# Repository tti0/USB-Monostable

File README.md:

# USB-Monostable

- An in-line timer/monostable switch for 5 V USB power, with a PCB based around the [555 timer](https://www.ti.com/product/NE555) and [SiP32508 load switch](https://www.vishay.com/docs/62754/sip32508.pdf) ICs.

_Populated USB-Monostable PCB_

- Pressing the "On" button causes the switch between the input and output USB power lines to close, reopening after a customisable and fixed time period has elapsed.
- Pressing the "Reset" button causes the switch to immediately open.
- Optional indicator LED reflects the switch status.
- USB data lines are not passed through.
- Current draw when the switch is open is under than 1 mA at 5 V.
- Slim physical footprint (20 x 60 mm) allows the switch to be placed in-line, between a power supply and downstream device.
- Uses robust full-size USB-A 2.0 connectors: male for the input, female for the output.
- This is an open source hardware project: you can use the files in this repository to make your own switch, or modify the KiCAD PCB design as you see fit.

_Unpopulated USB-Monostable PCB_

## Usage

PCBs can be purchased from any fabricator by submitting the latest Gerber files from this repository (see the [Releases](https://github.com/tti0/USB-Monostable/releases) page). The footprints chosen (mostly SMD 0805) allow all components in the BOM to then be soldered by hand fairly easily. It is recommended to use lead-free solder of diameter 0.6 mm. 

The values of **R2** and **C2** may be adjusted to alter the time period (the length of time for which power is supplied to the output after the button is pressed) of the switch. Since this project uses the 555 timer, the standard monostable equation applies:

```
Time period (seconds) = R2 (Ohms) * C2 (Farads) * 1.1
```

The LED **D1** and its current-limiting resistor **R4** can be omitted during construction if a visual status indicator is not required.

### Bill of materials (BOM)

The USB connectors **J1** and **J2** are the only non-standard footprints in this project. Proprietary KiCAD footprints can be downloaded by following the links in the below table, but cannot be distributed with this project for licensing reasons.

Values of **R2** and **C2** listed here result in a time period of 39.6 seconds.

| Reference | Qty | Value                  | Footprint                           |
|-----------|-----|------------------------|-------------------------------------|
| C1        | 1   | 10 nF                  | Capacitor_SMD:C_0805_2012Metric     |
| C2        | 1   | 10 uF                  | Capacitor_SMD:C_0805_2012Metric     |
| C3        | 1   | 100 nF                 | Capacitor_SMD:C_0805_2012Metric     |
| C4        | 1   | 4.7 uF                 | Capacitor_SMD:C_0805_2012Metric     |
| D1        | 1   | LED (Green)            | LED_SMD:LED_0805_2012Metric         |
| IC1       | 1   | SIP32508DT-T1-GE3      | Package_TO_SOT_SMD:SOT-23-6         |
| J1        | 1   | USB_A (Input, male)    | [SamacSys_Parts:USB1061GFLA](https://www.mouser.co.uk/ProductDetail/640-USB1061-GF-L-A)          |
| J2        | 1   | USB_A (Output, female) | [SamacSys_Parts:USBASRA](https://www.mouser.co.uk/ProductDetail/737-USB-A-S-RA)              |
| R1, R3    | 2   | 10k                    | Resistor_SMD:R_0805_2012Metric      |
| R2        | 1   | 3M6                    | Resistor_SMD:R_0805_2012Metric      |
| R4        | 1   | 1k                     | Resistor_SMD:R_0805_2012Metric      |
| SW1       | 1   | SW_Push (Set)          | Button_Switch_THT:SW_PUSH_6mm       |
| SW2       | 1   | SW_Push (Reset)        | Button_Switch_THT:SW_PUSH_6mm       |
| U1        | 1   | NE555D                 | Package_SO:SOIC-8_3.9x4.9mm_P1.27mm |

## Licencing

This project is Copyright (c) tti0 2024, and licenced under the _CERN Open Hardware Licence Version 2 – Permissive_. Please see `LICENSE` for full details.

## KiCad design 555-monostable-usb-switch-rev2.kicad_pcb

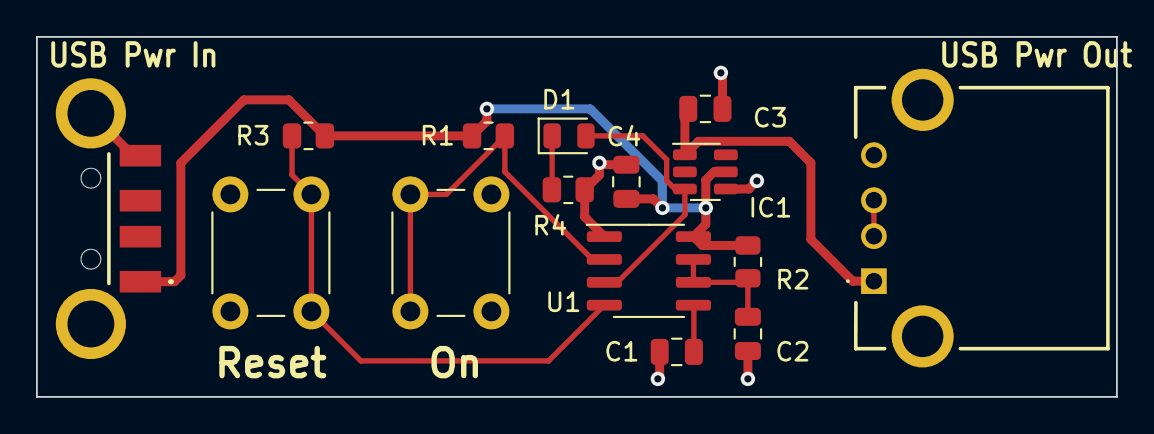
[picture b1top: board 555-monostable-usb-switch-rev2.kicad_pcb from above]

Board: 2 copper layers, 60.0 x 20.0 mm, 15 parts (0 on the bottom side), 10 nets.

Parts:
C1: 10 nF; C_0805_2012Metric
C2: 10 uF; C_0805_2012Metric
C3: 100 nF; C_0805_2012Metric
C4: 4.7 uF; C_0805_2012Metric
D1: LED; LED_0805_2012Metric
IC1: SIP32508DT-T1-GE3; SOT-23-6
J1: USB_A (Input, male); USB1061GFLA
J2: USB_A (Output, female); USBASRA
R1, R3: 10k; R_0805_2012Metric
R2: 5M6; R_0805_2012Metric
R4: 220; R_0805_2012Metric
SW1: SW_Push (Set); SW_PUSH_6mm
SW2: SW_Push (Reset); SW_PUSH_6mm
U1: NE555D; SOIC-8_3.9x4.9mm_P1.27mm

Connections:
+5V: C4.1, IC1.5 (IN_1), J1.1 (VBUS), R1.1, R2.1, R3.1, U1.8 (VCC)
GND: C1.1, C2.2, C3.2, C4.2, IC1.4 (GND), J1.4 (GND), J1.MH1, J1.MH4, J2.4 (GND), J2.MH1, J2.MH2, R4.2, SW1.1, SW2.1, U1.1 (GND)
unnamed: D1.1 (K), R4.1
unnamed: C3.1, IC1.1 (OUT_1), J2.1 (VBUS)
unnamed: J2.2 (D-), J2.3 (D+)
unnamed: C1.2, U1.5 (CV)
unnamed: C2.1, R2.2, U1.6 (THR), U1.7 (DIS)
unnamed: R3.2, SW2.2, U1.4 (R)
unnamed: R1.2, SW1.2, U1.2 (TR)
Timer_Enable: D1.2 (A), IC1.3 (EN), U1.3 (Q)

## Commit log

2024-05-18 Add Rev 2A files
